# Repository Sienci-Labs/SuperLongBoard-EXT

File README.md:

# SuperLongBoard-EXT PCB Design
Hardware repo for the SLB-EXT board for the AltMill. These are all the raw build files that we're making available to the public so you can see and access the work that's been put in to make the SuperLongBoard-EXT as it currently exists. If you'd like to make it yourself, modify it, or suggest improvements feel free. Please note and respect the license we've chosen to distribute it under.

# License

This code has been created within the context of Open Hardware and is licensed under the "CERN-OHL-S v2". Please read more about this in the LICENSE file. You could redistribute and modify this source and make products using it under the terms of the CERN-OHL-S v2. This means stuff like licensing your changes reciprocally, giving attribution to us, and releasing hardware that this code runs on as CERN-OHL-S v2 too. Note that this LICENSE applies on all coding work done in prior commits to-date, and is now being released in good faith that no action will be taken to pursue past work in order to duplicate the work we've put in without having to abide by the License that's now being applied at its first public release.

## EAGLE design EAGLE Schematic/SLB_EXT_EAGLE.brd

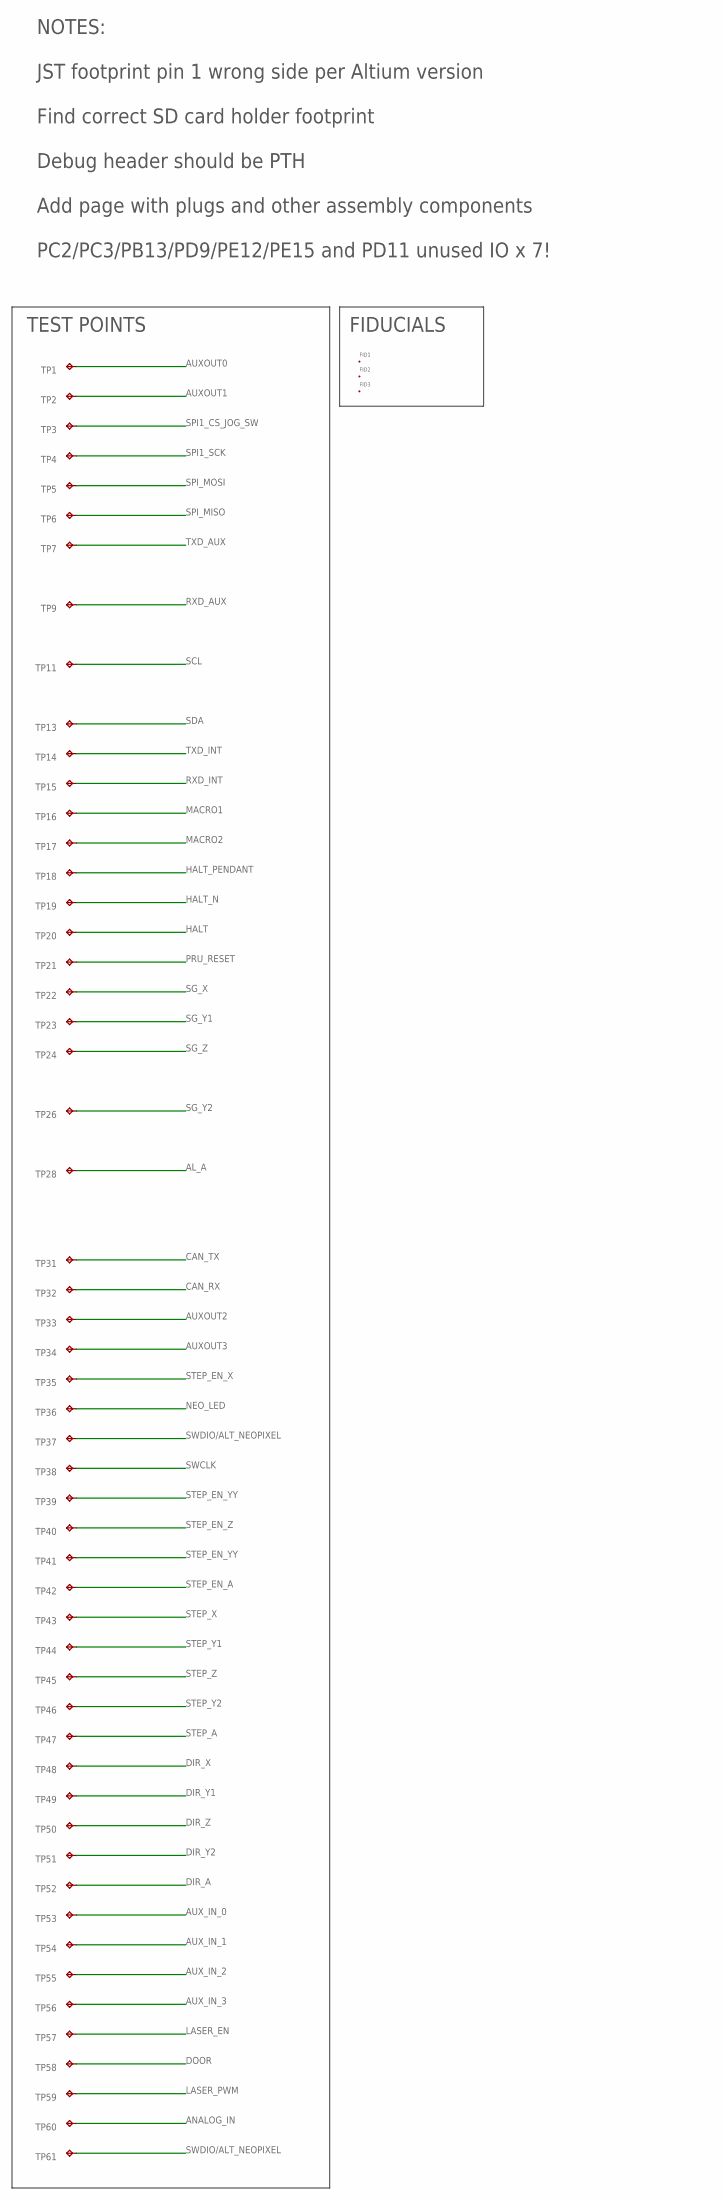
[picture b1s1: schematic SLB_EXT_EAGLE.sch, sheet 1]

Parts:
FID1, FID2, FID3: FID_40MIL_P; FID_040_P
TP1, TP2, TP3, TP4, TP5, TP6, TP7, TP9, TP11, TP13, TP14, TP15, TP16, TP17, TP18, TP19, TP20, TP21, TP22, TP23, TP24, TP26, TP28, TP31, TP32, TP33, TP34, TP35, TP36, TP37, TP38, TP39, TP40, TP41, TP42, TP43, TP44, TP45, TP46, TP47, TP48, TP49, TP50, TP51, TP52, TP53, TP54, TP55, TP56, TP57, TP58, TP59, TP60, TP61: TPB2,54; B2,54

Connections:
AL_A: TP28.TP; also elsewhere on the board
ANALOG_IN: TP60.TP; also elsewhere on the board
AUXOUT0: TP1.TP; also elsewhere on the board
AUXOUT1: TP2.TP; also elsewhere on the board
AUXOUT2: TP33.TP; also elsewhere on the board
AUXOUT3: TP34.TP; also elsewhere on the board
AUX_IN_0: TP53.TP; also elsewhere on the board
AUX_IN_1: TP54.TP; also elsewhere on the board
AUX_IN_2: TP55.TP; also elsewhere on the board
AUX_IN_3: TP56.TP; also elsewhere on the board
CAN_RX: TP32.TP; also elsewhere on the board
CAN_TX: TP31.TP; also elsewhere on the board
DIR_A: TP52.TP; also elsewhere on the board
DIR_X: TP48.TP; also elsewhere on the board
DIR_Y1: TP49.TP; also elsewhere on the board
DIR_Y2: TP51.TP; also elsewhere on the board
DIR_Z: TP50.TP; also elsewhere on the board
DOOR: TP58.TP; also elsewhere on the board
HALT: TP20.TP; also elsewhere on the board
HALT_N: TP19.TP; also elsewhere on the board
HALT_PENDANT: TP18.TP; also elsewhere on the board
LASER_EN: TP57.TP; also elsewhere on the board
LASER_PWM: TP59.TP; also elsewhere on the board
MACRO1: TP16.TP; also elsewhere on the board
MACRO2: TP17.TP; also elsewhere on the board
NEO_LED: TP36.TP; also elsewhere on the board
PRU_RESET: TP21.TP; also elsewhere on the board
RXD_AUX: TP9.TP; also elsewhere on the board
RXD_INT: TP15.TP; also elsewhere on the board
SCL: TP11.TP; also elsewhere on the board
SDA: TP13.TP; also elsewhere on the board
SG_X: TP22.TP; also elsewhere on the board
SG_Y1: TP23.TP; also elsewhere on the board
SG_Y2: TP26.TP; also elsewhere on the board
SG_Z: TP24.TP; also elsewhere on the board
SPI1_CS_JOG_SW: TP3.TP; also elsewhere on the board
SPI1_SCK: TP4.TP; also elsewhere on the board
SPI_MISO: TP6.TP; also elsewhere on the board
SPI_MOSI: TP5.TP; also elsewhere on the board
STEP_A: TP47.TP; also elsewhere on the board
STEP_EN_A: TP42.TP; also elsewhere on the board
STEP_EN_X: TP35.TP; also elsewhere on the board
STEP_EN_YY: TP39.TP, TP41.TP; also elsewhere on the board
STEP_EN_Z: TP40.TP; also elsewhere on the board
STEP_X: TP43.TP; also elsewhere on the board
STEP_Y1: TP44.TP; also elsewhere on the board
STEP_Y2: TP46.TP; also elsewhere on the board
STEP_Z: TP45.TP; also elsewhere on the board
SWCLK: TP38.TP; also elsewhere on the board
SWDIO/ALT_NEOPIXEL: TP37.TP, TP61.TP; also elsewhere on the board
TXD_AUX: TP7.TP; also elsewhere on the board
TXD_INT: TP14.TP; also elsewhere on the board

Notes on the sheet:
NOTES: JST footprint pin 1 wrong side per Altium version Find correct SD card holder footprint Debug header should be PTH Add page with plugs and other assembly components PC2/PC3/PB13/PD9/PE12/PE15 and PD11 unused IO x 7!
TEST POINTS
FIDUCIALS

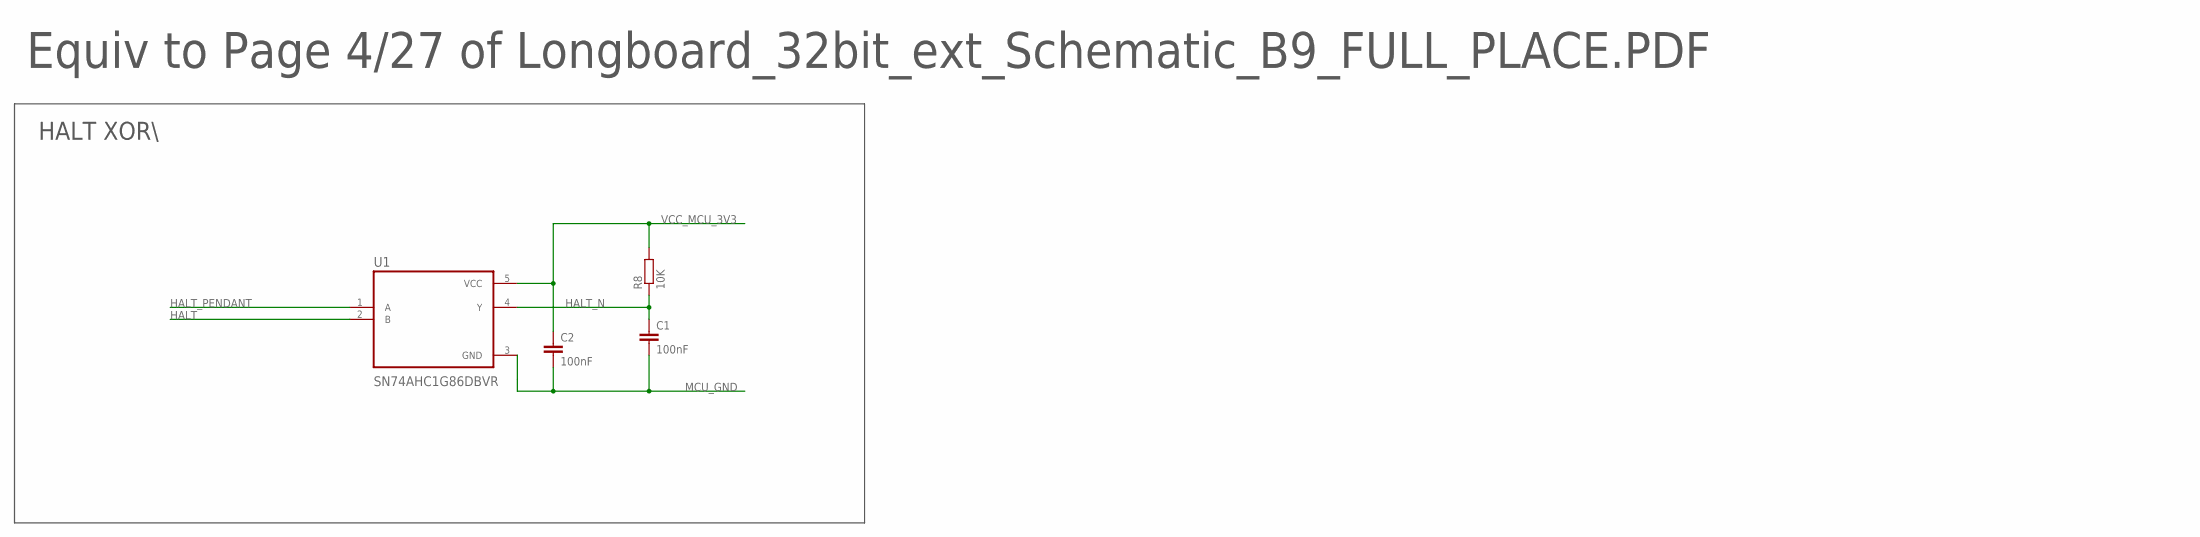
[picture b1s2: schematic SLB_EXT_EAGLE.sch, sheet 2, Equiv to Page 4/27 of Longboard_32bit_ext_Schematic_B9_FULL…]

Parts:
C1, C2: 100nF; C0402
R8: 10K; R0402
U1: SN74AHC1G86DBVR; SOT95P280X145-5N

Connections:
HALT: U1.2 (B); also elsewhere on the board
HALT_N: C1.1, R8.1, U1.4 (Y); also elsewhere on the board
HALT_PENDANT: U1.1 (A); also elsewhere on the board
MCU_GND: C1.2, C2.2, U1.3 (GND); also elsewhere on the board
VCC_MCU_3V3: C2.1, R8.2, U1.5 (VCC); also elsewhere on the board

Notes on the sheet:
Equiv to Page 4/27 of Longboard_32bit_ext_Schematic_B9_FULL_PLACE.PDF
HALT XOR\

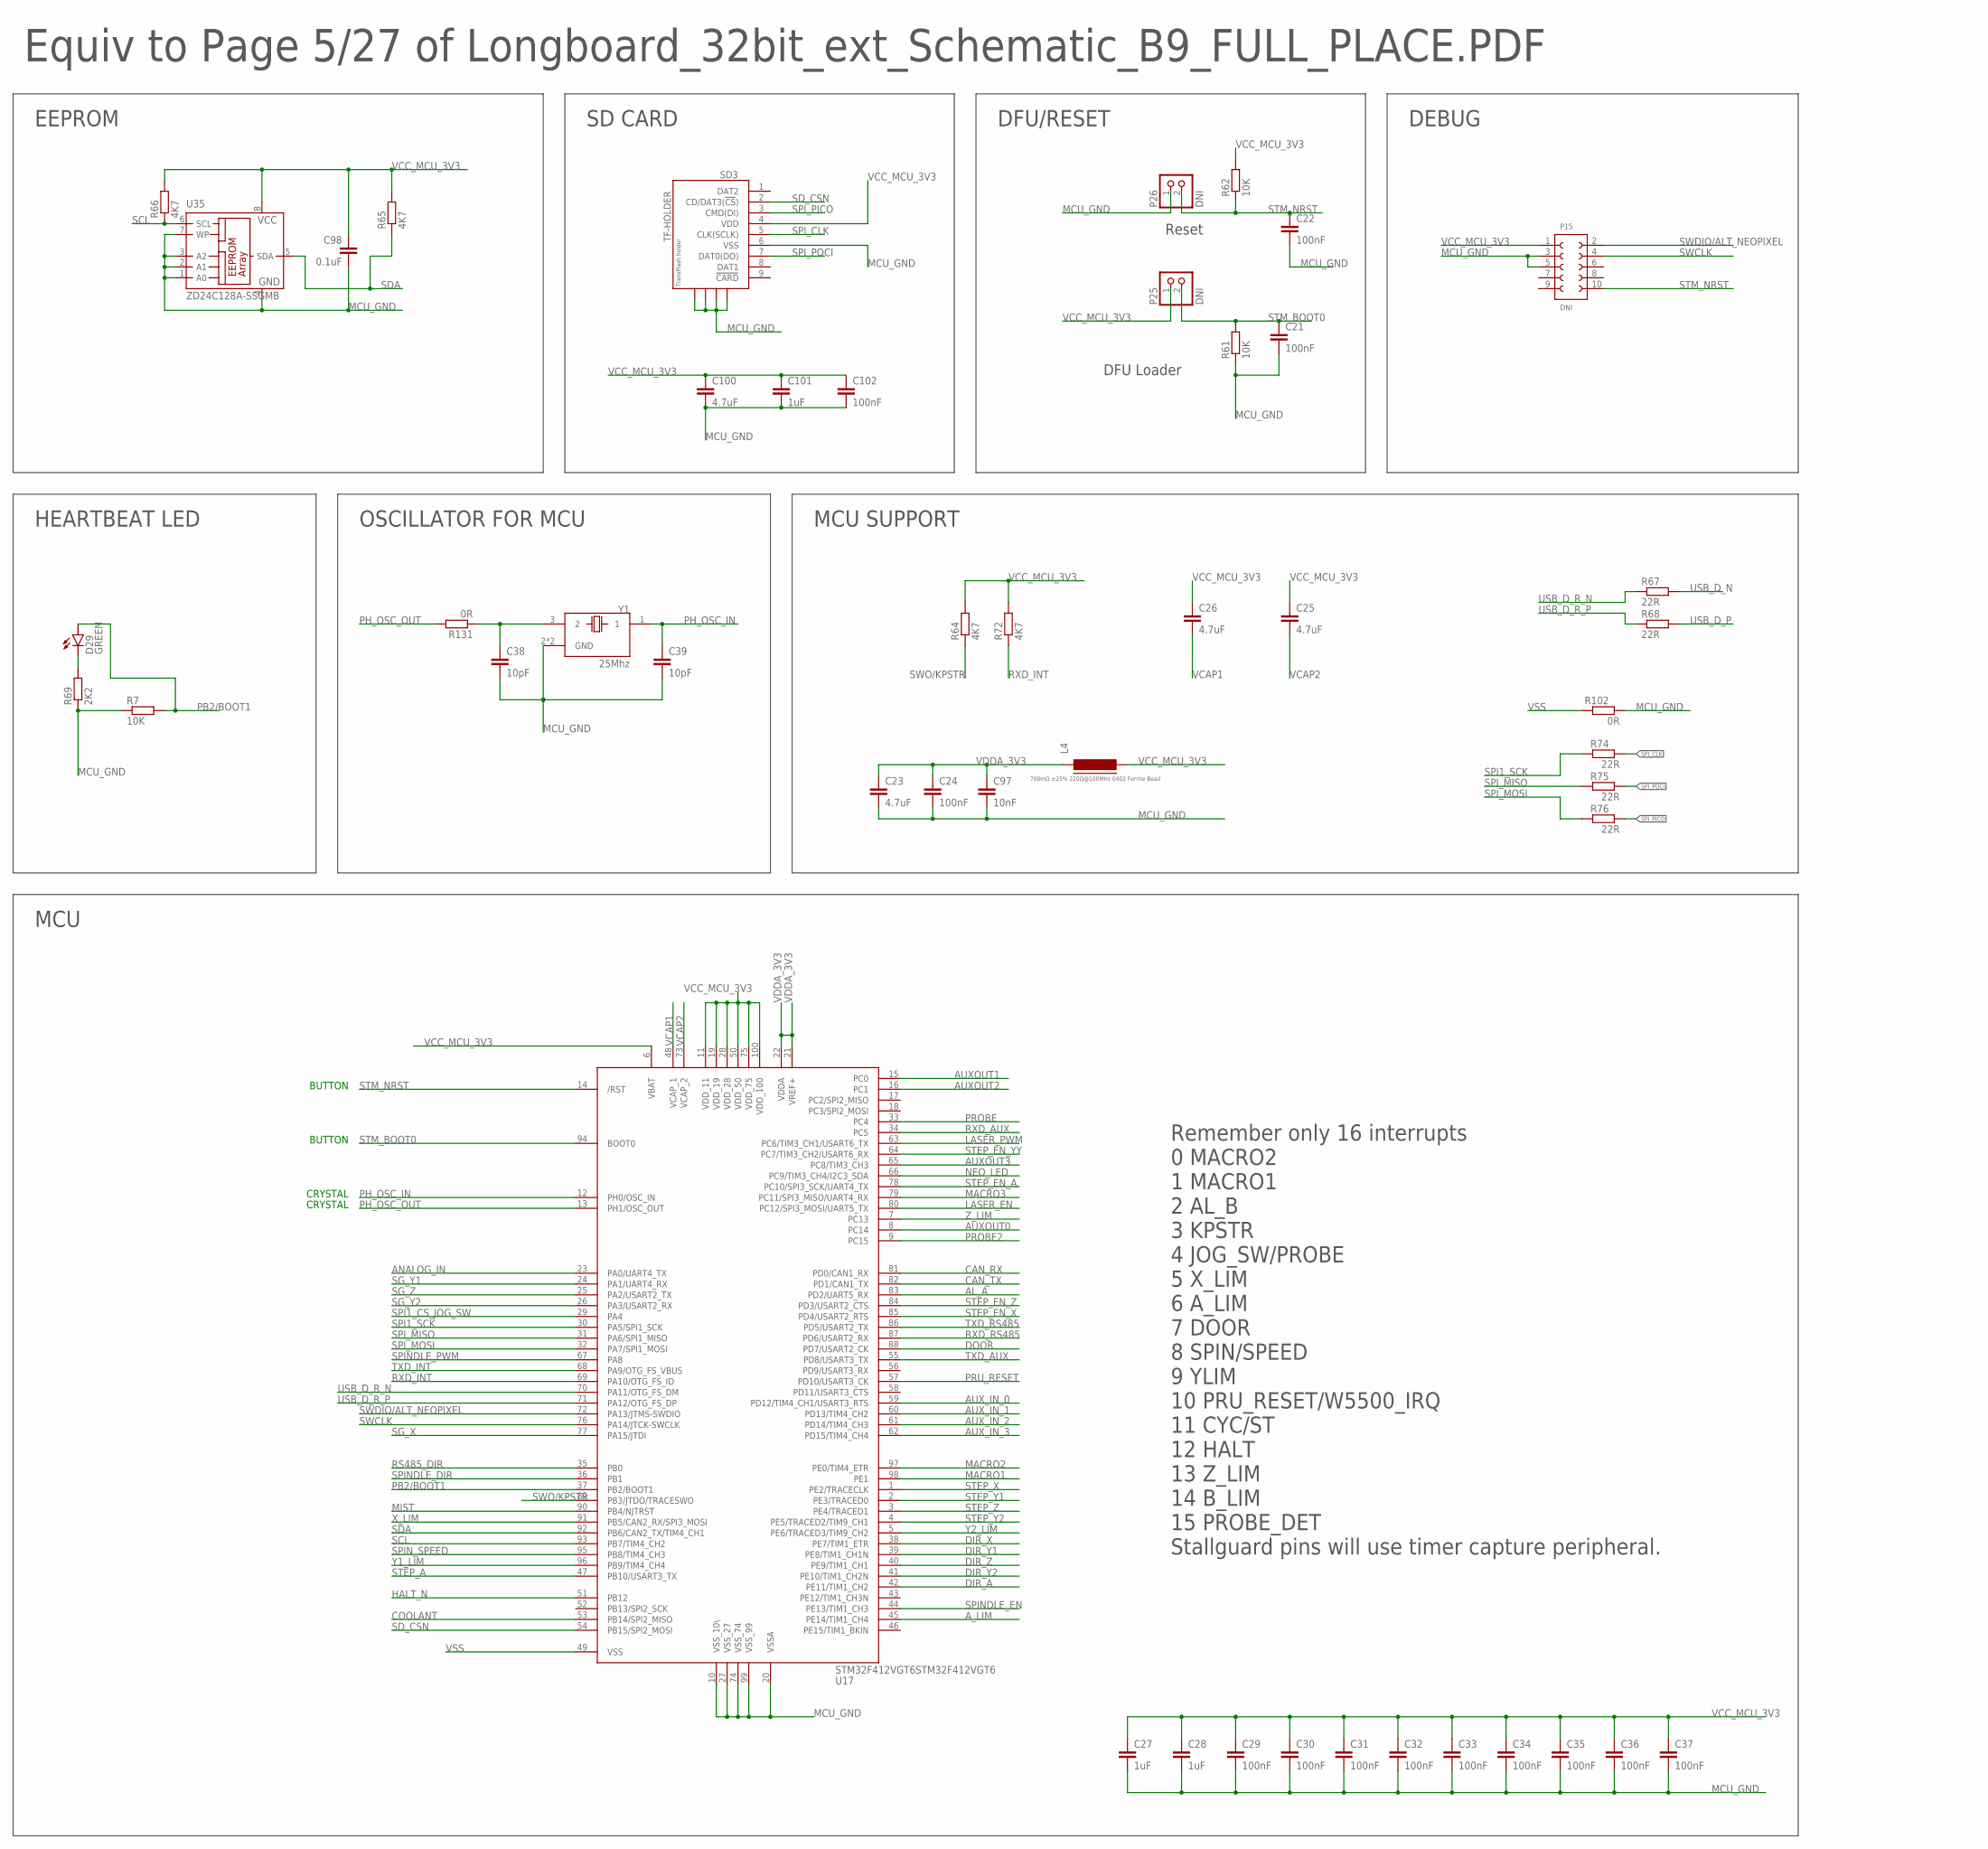
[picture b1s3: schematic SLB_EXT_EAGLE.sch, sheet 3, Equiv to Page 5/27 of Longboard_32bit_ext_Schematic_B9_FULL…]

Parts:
C21, C22, C24, C29, C30, C31, C32, C33, C34, C35, C36, C37, C102: 100nF; C0402
C23, C25, C26, C100: 4.7uF; C0603K
C27: 1uF; C0603
C28: 1uF; C0603K
C38, C39: 10pF; C0603K
C97: 10nF; C0402
C98: 0.1uF; 0805
C101: 1uF; C0402
D29: GREEN; CHIP-LED0603
L4: 700mΩ ±25% 220Ω@100MHz 0402 Ferrite Bead; FB402
P15: DNI; 621X1021021
P25, P26: DNI; 1X02
R7, R61, R62: 10K; R0402
R64, R65, R66, R72: 4K7; R0402
R67, R68, R74, R75, R76: 22R; R0603
R69: 2K2; R0402
R102, R131: 0R; R0603
SD3: TF-HOLDER; TF-PULL
U17: STM32F412VGT6STM32F412VGT6; LQFP100
U35: ZD24C128A-SSGMB; SO-08M
Y1: 25Mhz; XTAL_TSX-3225_16.0000MF18X-AC3

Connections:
AL_A: U17.83 (PD2/UART5_RX); also elsewhere on the board
ANALOG_IN: U17.23 (PA0/UART4_TX); also elsewhere on the board
AUXOUT0: U17.8 (PC14); also elsewhere on the board
AUXOUT1: U17.15 (PC0); also elsewhere on the board
AUXOUT2: U17.16 (PC1); also elsewhere on the board
AUXOUT3: U17.65 (PC8/TIM3_CH3); also elsewhere on the board
AUX_IN_0: U17.59 (PD12/TIM4_CH1/USART3_RTS); also elsewhere on the board
AUX_IN_1: U17.60 (PD13/TIM4_CH2); also elsewhere on the board
AUX_IN_2: U17.61 (PD14/TIM4_CH3); also elsewhere on the board
AUX_IN_3: U17.62 (PD15/TIM4_CH4); also elsewhere on the board
A_LIM: U17.45 (PE14/TIM1_CH4); also elsewhere on the board
CAN_RX: U17.81 (PD0/CAN1_RX); also elsewhere on the board
CAN_TX: U17.82 (PD1/CAN1_TX); also elsewhere on the board
COOLANT: U17.53 (PB14/SPI2_MISO); also elsewhere on the board
DIR_A: U17.42 (PE11/TIM1_CH2); also elsewhere on the board
DIR_X: U17.38 (PE7/TIM1_ETR); also elsewhere on the board
DIR_Y1: U17.39 (PE8/TIM1_CH1N); also elsewhere on the board
DIR_Y2: U17.41 (PE10/TIM1_CH2N); also elsewhere on the board
DIR_Z: U17.40 (PE9/TIM1_CH1); also elsewhere on the board
DOOR: U17.88 (PD7/USART2_CK); also elsewhere on the board
HALT_N: U17.51 (PB12); also elsewhere on the board
LASER_EN: U17.80 (PC12/SPI3_MOSI/UART5_TX); also elsewhere on the board
LASER_PWM: U17.63 (PC6/TIM3_CH1/USART6_TX); also elsewhere on the board
MACRO1: U17.98 (PE1); also elsewhere on the board
MACRO2: U17.97 (PE0/TIM4_ETR); also elsewhere on the board
MACRO3: U17.79 (PC11/SPI3_MISO/UART4_RX); also elsewhere on the board
MCU_GND: C21.2, C22.2, C23.2, C24.2, C27.2, C28.2, C29.2, C30.2, C31.2, C32.2, C33.2, C34.2, C35.2, C36.2, C37.2, C38.2, C39.2, C97.2, C98.2, C100.2, C101.2, C102.2, P15.3 (2), P15.5 (3), P26.1, R7.1, R61.1, R69.1, R102.1, SD3.6 (VSS), SD3.S1, SD3.S2, SD3.S3, SD3.S4, U17.10 (VSS_10\), U17.20 (VSSA), U17.27 (VSS_27), U17.74 (VSS_74), U17.99 (VSS_99), U35.1 (A0), U35.2 (A1), U35.3 (A2), U35.4 (GND), U35.7 (WP), Y1.2 (GND), Y1.4 (GND); also elsewhere on the board
MIST: U17.90 (PB4/NJTRST); also elsewhere on the board
unnamed: C38.1, R131.1, Y1.3 (2)
unnamed: D29.C, R69.2
NEO_LED: U17.66 (PC9/TIM3_CH4/I2C3_SDA); also elsewhere on the board
PB2/BOOT1: D29.A, R7.2, U17.37 (PB2/BOOT1)
PH_OSC_IN: C39.1, U17.12 (PH0/OSC_IN), Y1.1
PH_OSC_OUT: R131.2, U17.13 (PH1/OSC_OUT)
PROBE: U17.33 (PC4); also elsewhere on the board
PROBE2: U17.9 (PC15); also elsewhere on the board
PRU_RESET: U17.57 (PD10/USART3_CK); also elsewhere on the board
RS485_DIR: U17.35 (PB0); also elsewhere on the board
RXD_AUX: U17.34 (PC5); also elsewhere on the board
RXD_INT: R72.1, U17.69 (PA10/OTG_FS_ID); also elsewhere on the board
RXD_RS485: U17.87 (PD6/USART2_RX); also elsewhere on the board
SCL: R66.1, U17.93 (PB7/TIM4_CH2), U35.6 (SCL); also elsewhere on the board
SDA: R65.1, U17.92 (PB6/CAN2_TX/TIM4_CH1), U35.5 (SDA); also elsewhere on the board
SD_CSN: SD3.2 (CD/DAT3(!CS!)), U17.54 (PB15/SPI2_MOSI)
SG_X: U17.77 (PA15/JTDI); also elsewhere on the board
SG_Y1: U17.24 (PA1/UART4_RX); also elsewhere on the board
SG_Y2: U17.26 (PA3/USART2_RX); also elsewhere on the board
SG_Z: U17.25 (PA2/USART2_TX); also elsewhere on the board
SPI1_CS_JOG_SW: U17.29 (PA4); also elsewhere on the board
SPI1_SCK: R74.2, U17.30 (PA5/SPI1_SCK); also elsewhere on the board
SPINDLE_DIR: U17.36 (PB1); also elsewhere on the board
SPINDLE_EN: U17.44 (PE13/TIM1_CH3); also elsewhere on the board
SPINDLE_PWM: U17.67 (PA8); also elsewhere on the board
SPIN_SPEED: U17.95 (PB8/TIM4_CH3); also elsewhere on the board
SPI_CLK: R74.1, SD3.5 (CLK(SCLK)); also elsewhere on the board
SPI_MISO: R75.2, U17.31 (PA6/SPI1_MISO); also elsewhere on the board
SPI_MOSI: R76.2, U17.32 (PA7/SPI1_MOSI); also elsewhere on the board
SPI_PICO: R76.1, SD3.3 (CMD(DI)); also elsewhere on the board
SPI_POCI: R75.1, SD3.7 (DAT0(DO)); also elsewhere on the board
STEP_A: U17.47 (PB10/USART3_TX); also elsewhere on the board
STEP_EN_A: U17.78 (PC10/SPI3_SCK/UART4_TX); also elsewhere on the board
STEP_EN_X: U17.85 (PD4/USART2_RTS); also elsewhere on the board
STEP_EN_YY: U17.64 (PC7/TIM3_CH2/USART6_RX); also elsewhere on the board
STEP_EN_Z: U17.84 (PD3/USART2_CTS); also elsewhere on the board
STEP_X: U17.1 (PE2/TRACECLK); also elsewhere on the board
STEP_Y1: U17.2 (PE3/TRACED0); also elsewhere on the board
STEP_Y2: U17.4 (PE5/TRACED2/TIM9_CH1); also elsewhere on the board
STEP_Z: U17.3 (PE4/TRACED1); also elsewhere on the board
STM_BOOT0: C21.1, P25.2, R61.2, U17.94 (BOOT0); also elsewhere on the board
STM_NRST: C22.1, P15.10 (6), P26.2, R62.1, U17.14 (/RST); also elsewhere on the board
SWCLK: P15.4 (9), U17.76 (PA14/JTCK-SWCLK); also elsewhere on the board
SWDIO/ALT_NEOPIXEL: P15.2 (10), U17.72 (PA13/JTMS-SWDIO); also elsewhere on the board
SWO/KPSTR: R64.1, U17.89 (PB3/JTDO/TRACESWO)
TXD_AUX: U17.55 (PD8/USART3_TX); also elsewhere on the board
TXD_INT: U17.68 (PA9/OTG_FS_VBUS); also elsewhere on the board
TXD_RS485: U17.86 (PD5/USART2_TX); also elsewhere on the board
USB_D_N: R67.2; also elsewhere on the board
USB_D_P: R68.2; also elsewhere on the board
USB_D_R_N: R67.1, U17.70 (PA11/OTG_FS_DM)
USB_D_R_P: R68.1, U17.71 (PA12/OTG_FS_DP)
VCAP1: C26.2, U17.48 (VCAP_1)
VCAP2: C25.2, U17.73 (VCAP_2)
VCC_MCU_3V3: C25.1, C26.1, C27.1, C28.1, C29.1, C30.1, C31.1, C32.1, C33.1, C34.1, C35.1, C36.1, C37.1, C98.1, C100.1, C101.1, C102.1, L4.2, P15.1, P25.1, R62.2, R64.2, R65.2, R66.2, R72.2, SD3.4 (VDD), U17.6 (VBAT), U17.11 (VDD_11), U17.19 (VDD_19), U17.28 (VDD_28), U17.50 (VDD_50), U17.75 (VDD_75), U17.100 (VDD_100), U35.8 (VCC); also elsewhere on the board
VDDA_3V3: C23.1, C24.1, C97.1, L4.1, U17.21 (VREF+), U17.22 (VDDA)
VSS: R102.2, U17.49 (VSS)
X_LIM: U17.91 (PB5/CAN2_RX/SPI3_MOSI); also elsewhere on the board
Y1_LIM: U17.96 (PB9/TIM4_CH4); also elsewhere on the board
Y2_LIM: U17.5 (PE6/TRACED3/TIM9_CH2); also elsewhere on the board
Z_LIM: U17.7 (PC13); also elsewhere on the board

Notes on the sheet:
Reset
DFU Loader
CRYSTAL
BUTTON
Equiv to Page 5/27 of Longboard_32bit_ext_Schematic_B9_FULL_PLACE.PDF
EEPROM
SD CARD
DFU/RESET
DEBUG
HEARTBEAT LED
OSCILLATOR FOR MCU
MCU SUPPORT
MCU
Remember only 16 interrupts 0 MACRO2 1 MACRO1 2 AL_B 3 KPSTR 4 JOG_SW/PROBE 5 X_LIM 6 A_LIM 7 DOOR 8 SPIN/SPEED 9 YLIM 10 PRU_RESET/W5500_IRQ 11 CYC/ST 12 HALT 13 Z_LIM 14 B_LIM 15 PROBE_DET Stallguard pins will use timer capture peripheral.

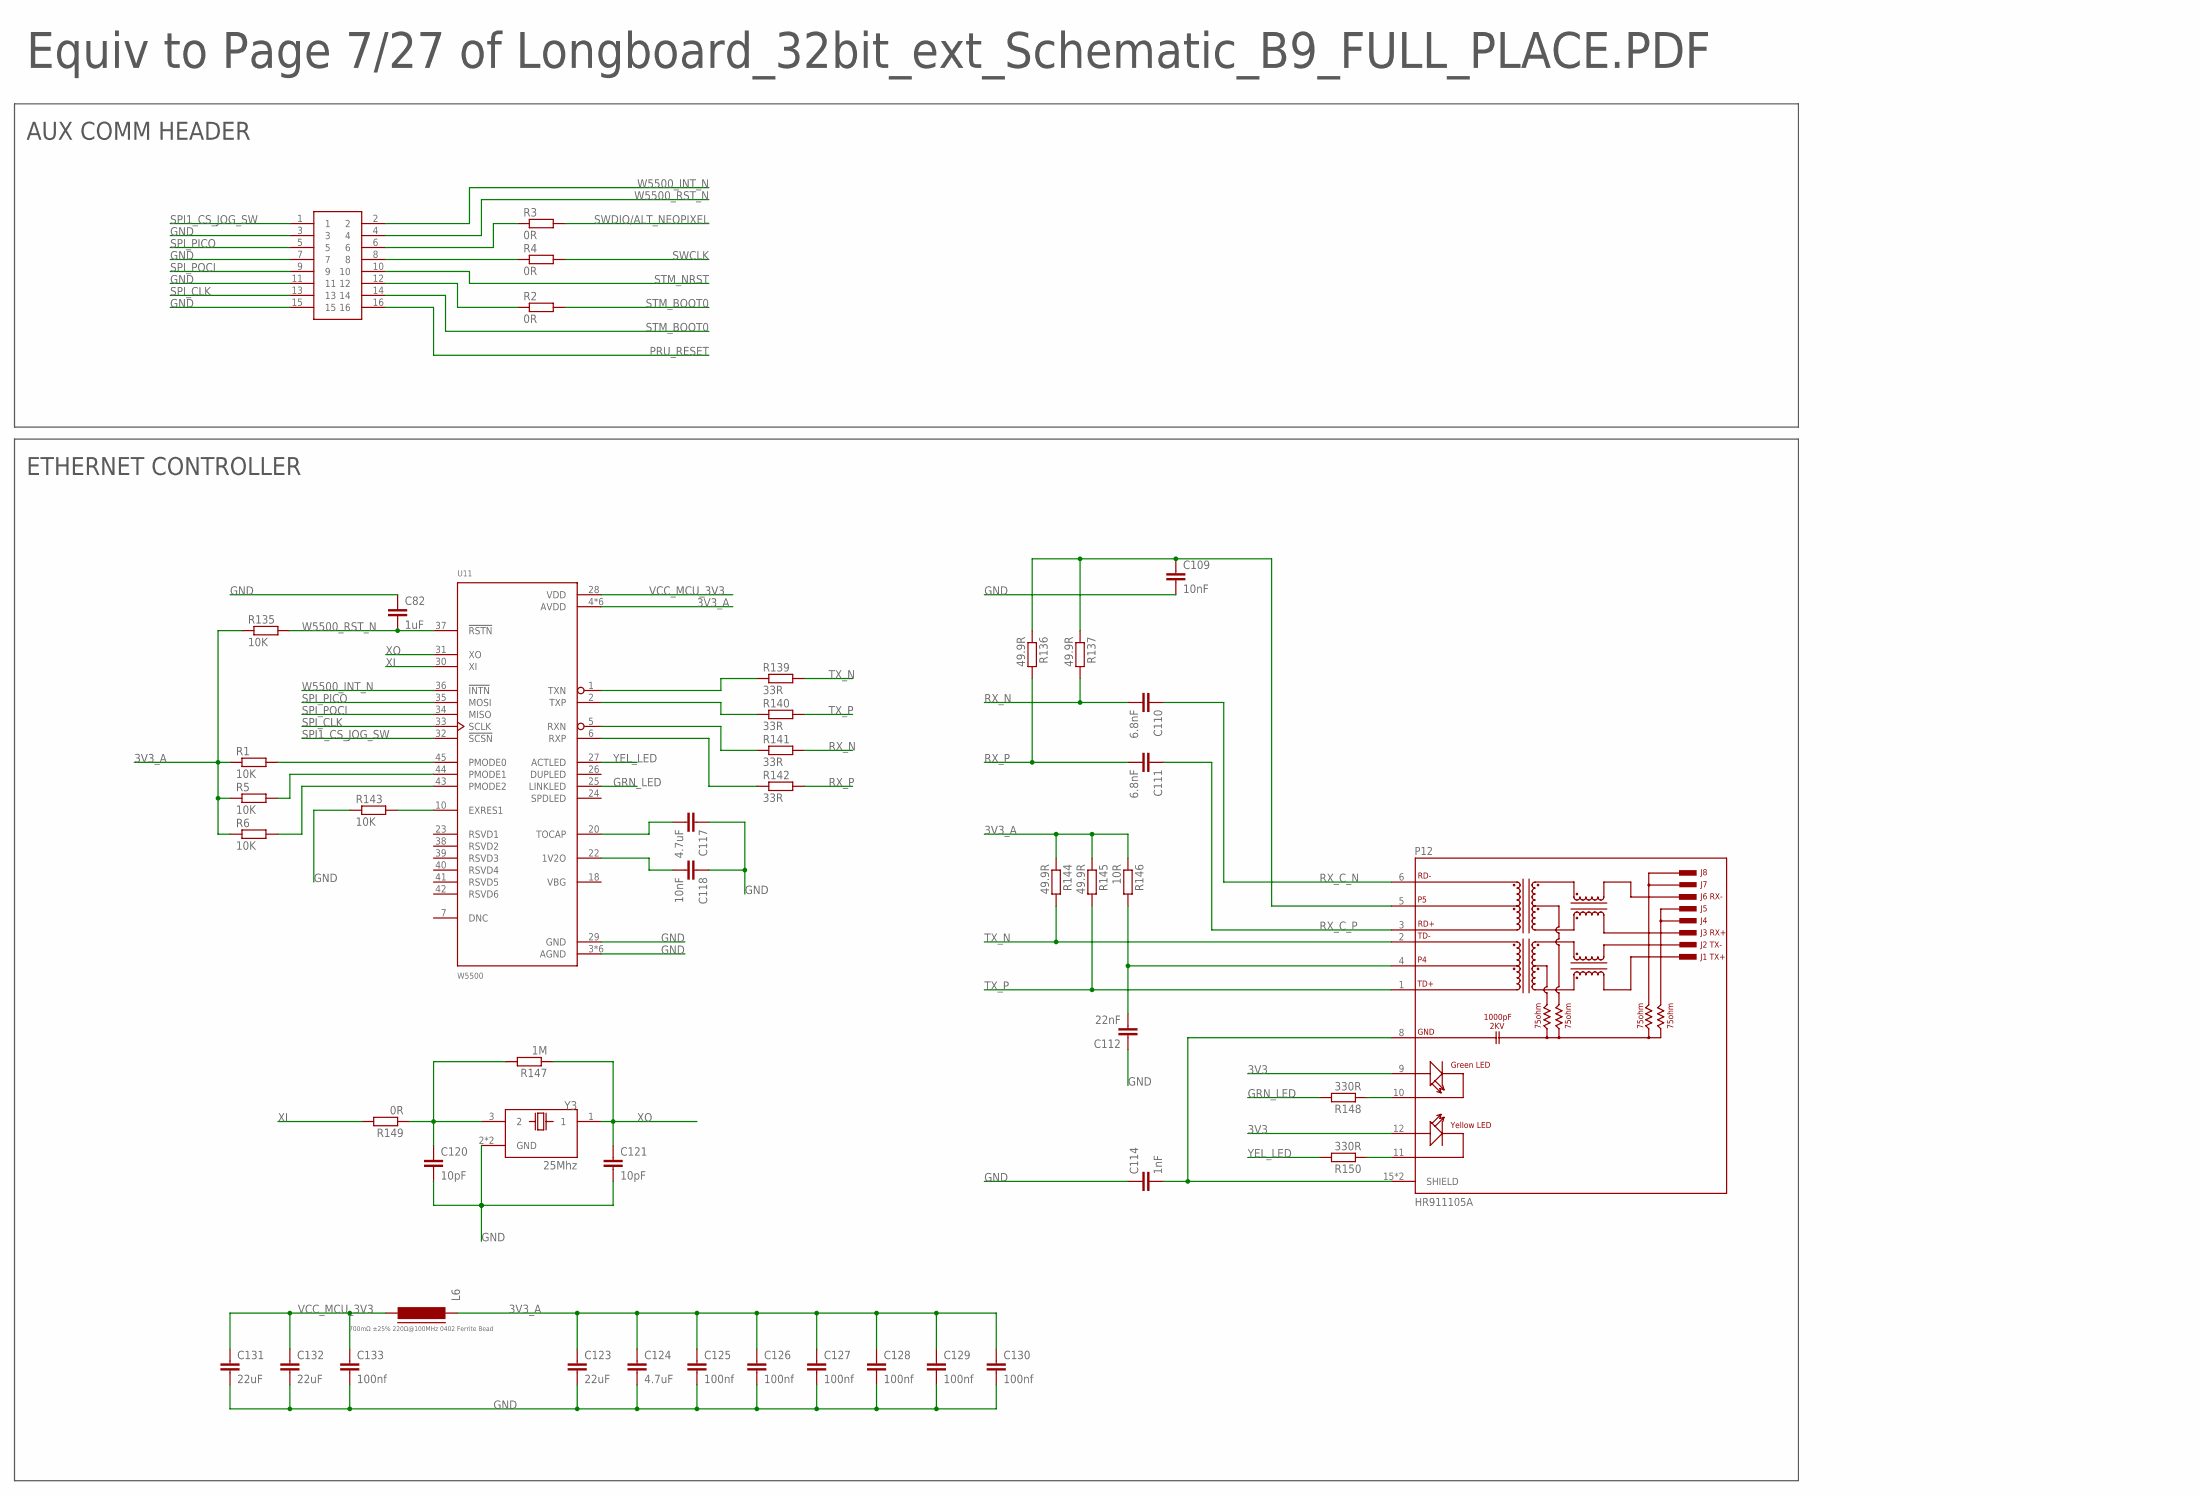
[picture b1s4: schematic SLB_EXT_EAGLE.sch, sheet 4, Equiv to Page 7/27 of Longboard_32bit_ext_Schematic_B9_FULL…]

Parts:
C82: 1uF; C0402
C109, C118: 10nF; C0402
C110, C111: 6.8nF; C0402
C112: 22nF; C0402
C114: 1nF; C1206
C117: 4.7uF; C0402
C120, C121: 10pF; C0402
C123, C131, C132: 22uF; C0603K
C124: 4.7uF; C0603K
C125, C126, C127, C129, C130, C133: 100nf; C0402
C128: 100nf; C0603K
J1: 16P_HEADER_SMD; 16_PIN_SMD_PIN_HEADER
L6: 700mΩ ±25% 220Ω@100MHz 0402 Ferrite Bead; FB402
P12: HR911105A; HANRUN_HR911105A
R1, R5, R6, R135: 10K; R0402
R2, R3, R4: 0R; R0603
R136, R137, R144, R145: 49.9R; R0402
R139, R140, R141, R142: 33R; R0402
R143: 10K; R0603
R146: 10R; R0402
R147: 1M; R0402
R148, R150: 330R; R0402
R149: 0R; R0402
U11: W5500; QFP50P900X900X160-48N
Y3: 25Mhz; XTAL_TSX-3225_16.0000MF18X-AC3

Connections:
3V3: P12.9 (GA), P12.12 (YA)
3V3_A: C123.1, C124.1, C125.1, C126.1, C127.1, C128.1, C129.1, C130.1, L6.1, R1.1, R5.1, R6.1, R135.1, R144.1, R145.1, R146.1, U11.4 (AVDD), U11.8 (AVDD), U11.11 (AVDD), U11.15 (AVDD), U11.17 (AVDD), U11.21 (AVDD)
GND: C82.1, C109.2, C112.1, C114.1, C117.1, C118.1, C120.2, C121.2, C123.2, C124.2, C125.2, C126.2, C127.2, C128.2, C129.2, C130.2, C131.2, C132.2, C133.2, J1.3, J1.7, J1.11, J1.15, R143.1, U11.3 (AGND), U11.9 (AGND), U11.14 (AGND), U11.16 (AGND), U11.19 (AGND), U11.29 (GND), U11.48 (AGND), Y3.2 (GND), Y3.4 (GND); also elsewhere on the board
GRN_LED: R148.2, U11.25 (LINKLED)
unnamed: P12.11 (YC), R150.1
unnamed: P12.10 (GC), R148.1
unnamed: C114.2, P12.8 (GND), P12.15 (SHIELD), P12.16 (SHIELD)
unnamed: C120.1, R147.2, R149.1, Y3.3 (2)
unnamed: C112.2, P12.4, R146.2
unnamed: R139.1, U11.1 (TXN)
unnamed: R140.1, U11.2 (TXP)
unnamed: C109.1, P12.5, R136.1, R137.1
unnamed: R141.1, U11.5 (RXN)
unnamed: R142.1, U11.6 (RXP)
unnamed: R143.2, U11.10 (EXRES1)
unnamed: C117.2, U11.20 (TOCAP)
unnamed: C118.2, U11.22 (1V2O)
unnamed: R6.2, U11.43 (PMODE2)
unnamed: R5.2, U11.44 (PMODE1)
unnamed: R1.2, U11.45 (PMODE0)
unnamed: J1.6, R3.1
unnamed: J1.8, R4.1
unnamed: J1.12, R2.1
PRU_RESET: J1.16; also elsewhere on the board
RX_C_N: C110.1, P12.6 (RD-)
RX_C_P: C111.1, P12.3 (RD+)
RX_N: C110.2, R137.2, R141.2
RX_P: C111.2, R136.2, R142.2
SPI1_CS_JOG_SW: J1.1, U11.32 (!SCSN); also elsewhere on the board
SPI_CLK: J1.13, U11.33 (SCLK); also elsewhere on the board
SPI_PICO: J1.5, U11.35 (MOSI); also elsewhere on the board
SPI_POCI: J1.9, U11.34 (MISO); also elsewhere on the board
STM_BOOT0: J1.14, R2.2; also elsewhere on the board
STM_NRST: J1.10; also elsewhere on the board
SWCLK: R4.2; also elsewhere on the board
SWDIO/ALT_NEOPIXEL: R3.2; also elsewhere on the board
TX_N: P12.2 (TD-), R139.2, R144.2
TX_P: P12.1 (TD+), R140.2, R145.2
VCC_MCU_3V3: C131.1, C132.1, C133.1, L6.2, U11.28 (VDD); also elsewhere on the board
W5500_INT_N: J1.2, U11.36 (!INTN)
W5500_RST_N: C82.2, J1.4, R135.2, U11.37 (!RSTN)
XI: R149.2, U11.30 (XI)
XO: C121.1, R147.1, U11.31 (XO), Y3.1
YEL_LED: R150.2, U11.27 (ACTLED)

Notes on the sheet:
Equiv to Page 7/27 of Longboard_32bit_ext_Schematic_B9_FULL_PLACE.PDF
ETHERNET CONTROLLER
AUX COMM HEADER

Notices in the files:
parts and their libraries:
vovtech: Licensing: CC v3.0 Share-Alike You are welcome to use this library for commercial purposes.
SparkFun-Connectors: Licensing: Creative Commons ShareAlike 4.0 International - https://creativecommons.org/licenses/by-sa/4.0
Eagle_BOARD-TO-BOARD_CONNECTORS: Copyright: Würth Elektronik
